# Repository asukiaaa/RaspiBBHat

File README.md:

# RaspiBBHat

A Raspberry Pi Hat for a mini bread board.

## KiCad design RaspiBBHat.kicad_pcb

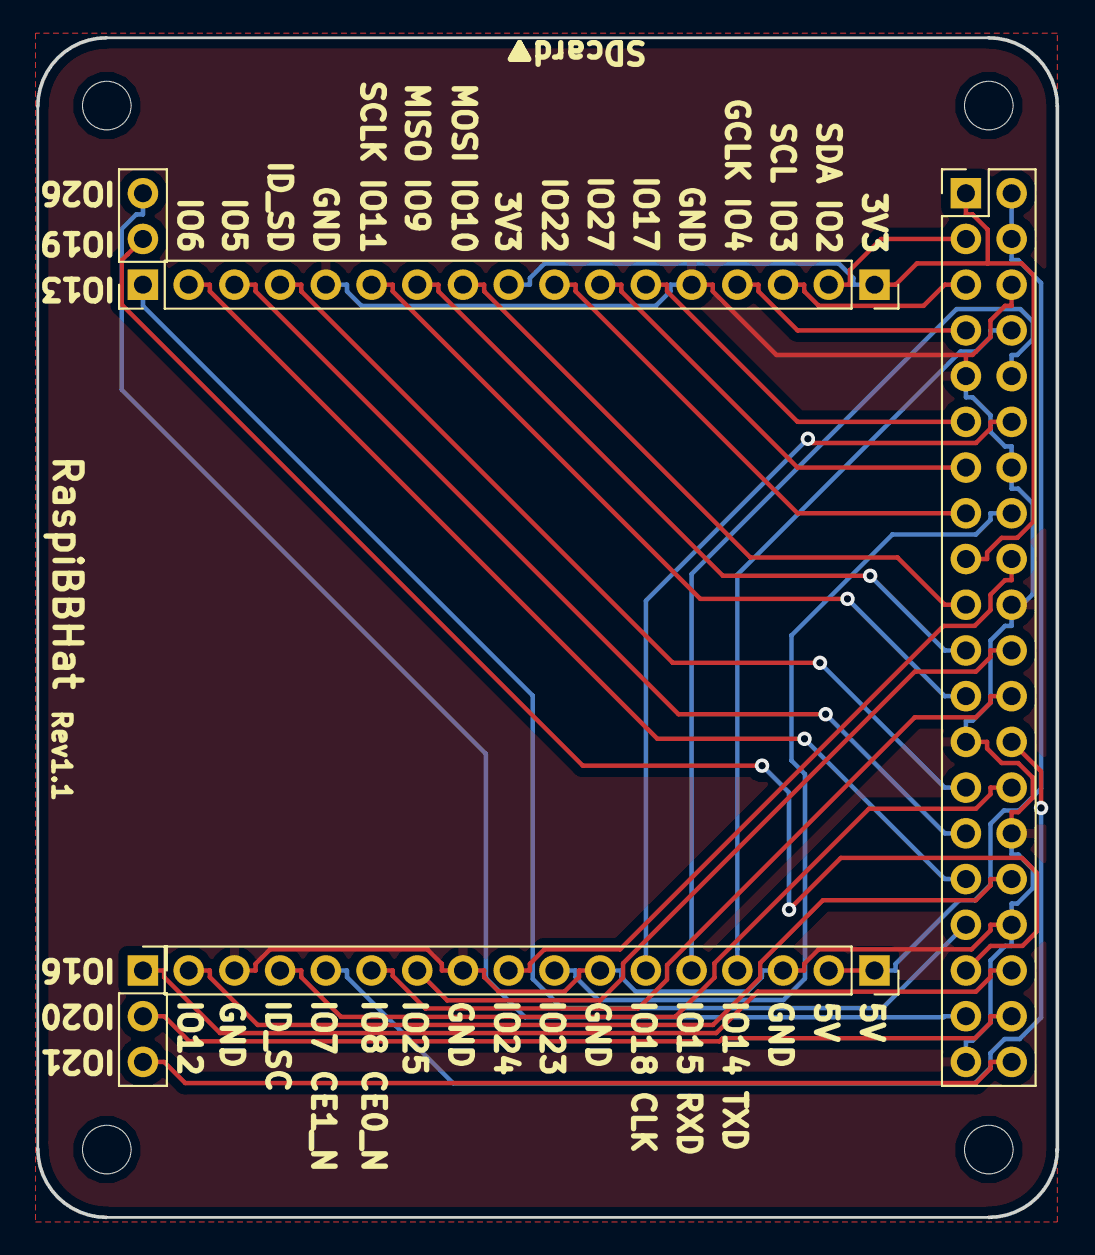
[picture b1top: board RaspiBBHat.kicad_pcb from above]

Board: 2 copper layers, 56.6 x 65.5 mm, 9 parts (0 on the bottom side), 31 nets.

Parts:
J1, J3: Conn_01x03; PinSocket_1x03_P2.54mm_Vertical
J2, J4: Conn_01x16; PinSocket_1x16_P2.54mm_Vertical
J5: Raspberry_Pi_2_3; PinHeader_2x20_P2.54mm_Vertical
REF1, REF2, REF3, REF4: MountingHole_2.7mm

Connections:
+3V3: J2.1, J2.9, J5.1, J5.17
+5C: J4.1, J4.2, J5.2, J5.4
GND: J2.5, J2.13, J4.3, J4.7, J4.10, J4.15, J5.6, J5.9, J5.14, J5.20, J5.25, J5.30, J5.34, J5.39
GPIO2(SDA1): J2.2, J5.3
GPIO3(SCL1): J2.3, J5.5
GPIO4(GCLK): J2.4, J5.7
GPIO5: J2.15, J5.29
GPIO6: J2.16, J5.31
GPIO7(SPI_CE1): J4.13, J5.26
GPIO8(SPI_CE0): J4.12, J5.24
GPIO9(SPI_MISO): J2.11, J5.21
GPIO10(SPI_MOSI): J2.10, J5.19
GPIO11(SPI_SCLK): J2.12, J5.23
GPIO12: J4.16, J5.32
GPIO13: J1.1, J5.33
GPIO14(TXD): J4.4, J5.8
GPIO15(RXD): J4.5, J5.10
GPIO16: J3.1, J5.36
GPIO17(GEN0): J2.6, J5.11
GPIO18(GEN1): J4.6, J5.12
GPIO19: J1.2, J5.35
GPIO20: J3.2, J5.38
GPIO21: J3.3, J5.40
GPIO22(GEN3): J2.8, J5.15
GPIO23(GEN4): J4.8, J5.16
GPIO24(GEN5): J4.9, J5.18
GPIO25(GEN6): J4.11, J5.22
GPIO26: J1.3, J5.37
GPIO27(GEN2): J2.7, J5.13
ID_SC: J4.14, J5.28
ID_SD: J2.14, J5.27

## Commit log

2018-03-29 Add license and image to readme
2018-04-09 Update plot files and preview image
2018-04-24 Apply larger clearance mounting holes
